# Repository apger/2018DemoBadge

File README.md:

# 2018DemoBadge
KiCad Project to test desired features for 2018 PCB badges

Initial goals for Apger/Lu:
1.  exposing graphics by keeping substrate off of the underlying copper
2.  masking over copper graphics for a raised 3d image/effect
3.  importing high res graphics as stencils
4.  using a high-res graphic outline for cutlines to make an interesting shape for a badge
5.

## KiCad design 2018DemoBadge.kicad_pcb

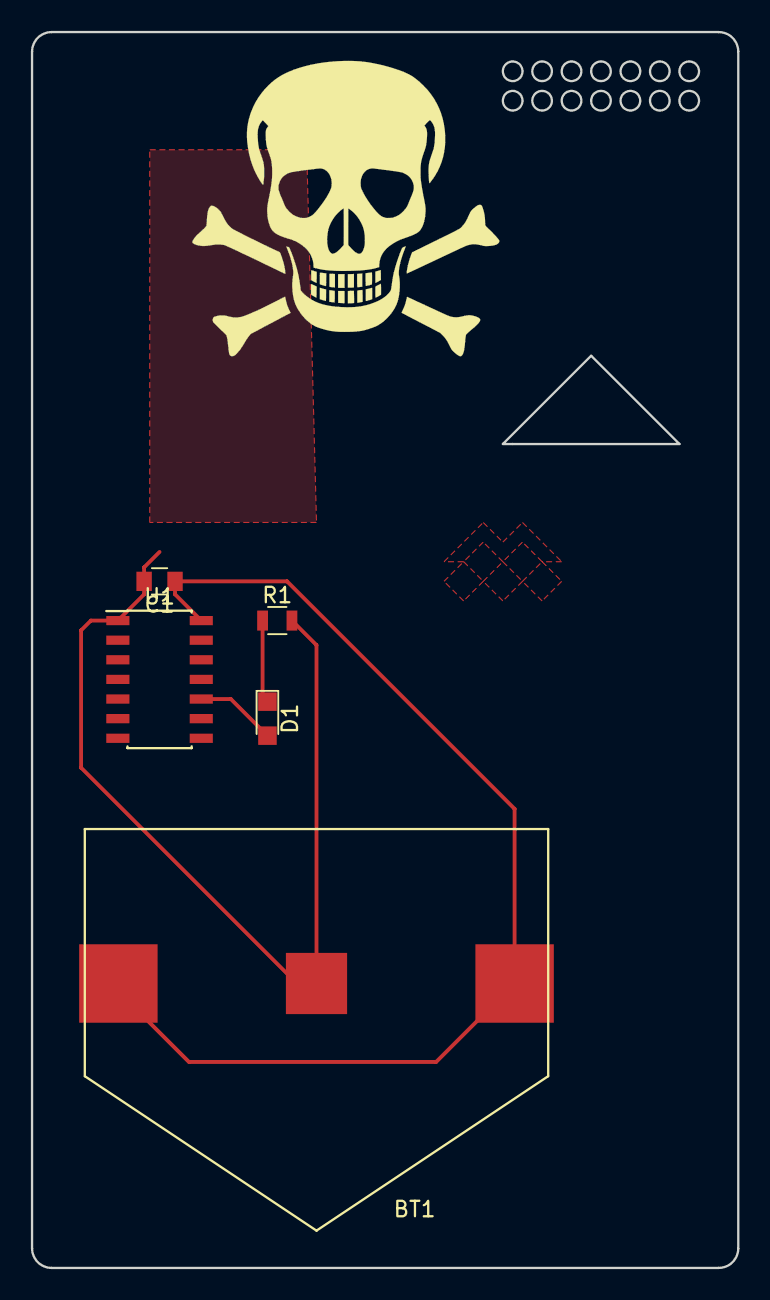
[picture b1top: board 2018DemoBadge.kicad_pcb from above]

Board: 2 copper layers, 45.7 x 80.0 mm, 5 parts (0 on the bottom side), 4 nets.

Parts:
BT1: Battery_Cell; BatteryHolder20mmSMD
C1: 1uF; C_0805
D1: LED; LED_0805
R1: 1k; R_0805
U1: PIC16F15325; SOIC-14_3.9x8.7mm_Pitch1.27mm

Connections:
/VSS: BT1.1, C1.1, U1.14
GND: BT1.2, C1.2, R1.2, U1.1
unnamed: D1.1, R1.1
unnamed: D1.2, U1.10

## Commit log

2017-12-20 initial commit of empty Kicad project
2017-12-20 Schema and footprint associations in place for simple pic16 led blinker
2017-12-21 First push from tong
2017-12-21 First commit from Tong
2017-12-22 removed old lib
2017-12-22 removed old lib again
2017-12-22 KiCad upgrade
2017-12-22 skulls
2017-12-22 skulls and copper fill zone unconnected
2017-12-24 graphics on back - smaller badge
2017-12-26 set for first test run of graphics
